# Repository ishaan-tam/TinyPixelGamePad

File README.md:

# TinyPixelGamePad
A tiny RP2040-powered handheld gamepad built around a custom SMD Neopixel matrix display. Designed to fit on a keychain and play simple retro-style games like Snake.

## Features
- Ultra-compact 20x12 Neopixel display using 1x1mm SMD LEDs
- RP2040 microcontroller
- Custom PCB designed in KiCad
- Programmed in Arduino
- USB-C power and programming
- Built-in games: Snake, with more to come

## Preview

## Repo Structure
- `Firmware/` – Game logic and display code (Arduino)
- `Hardware/` – KiCad schematics and PCB layout
- `Images/` – Rendered images and assembly photos
- `Docs/` – Build notes, game dev instructions

## Getting Started
1. Open `Firmware/snake.ino` in the Arduino IDE
2. Select the RP2040 board and upload via USB
3. Power on and start playing 

## Pin Mapping

## Roadmap
- Add menu for game selection
- Add buzzer for sound feedback
- Add charging support for LiPo battery
- Open-source arcade game template

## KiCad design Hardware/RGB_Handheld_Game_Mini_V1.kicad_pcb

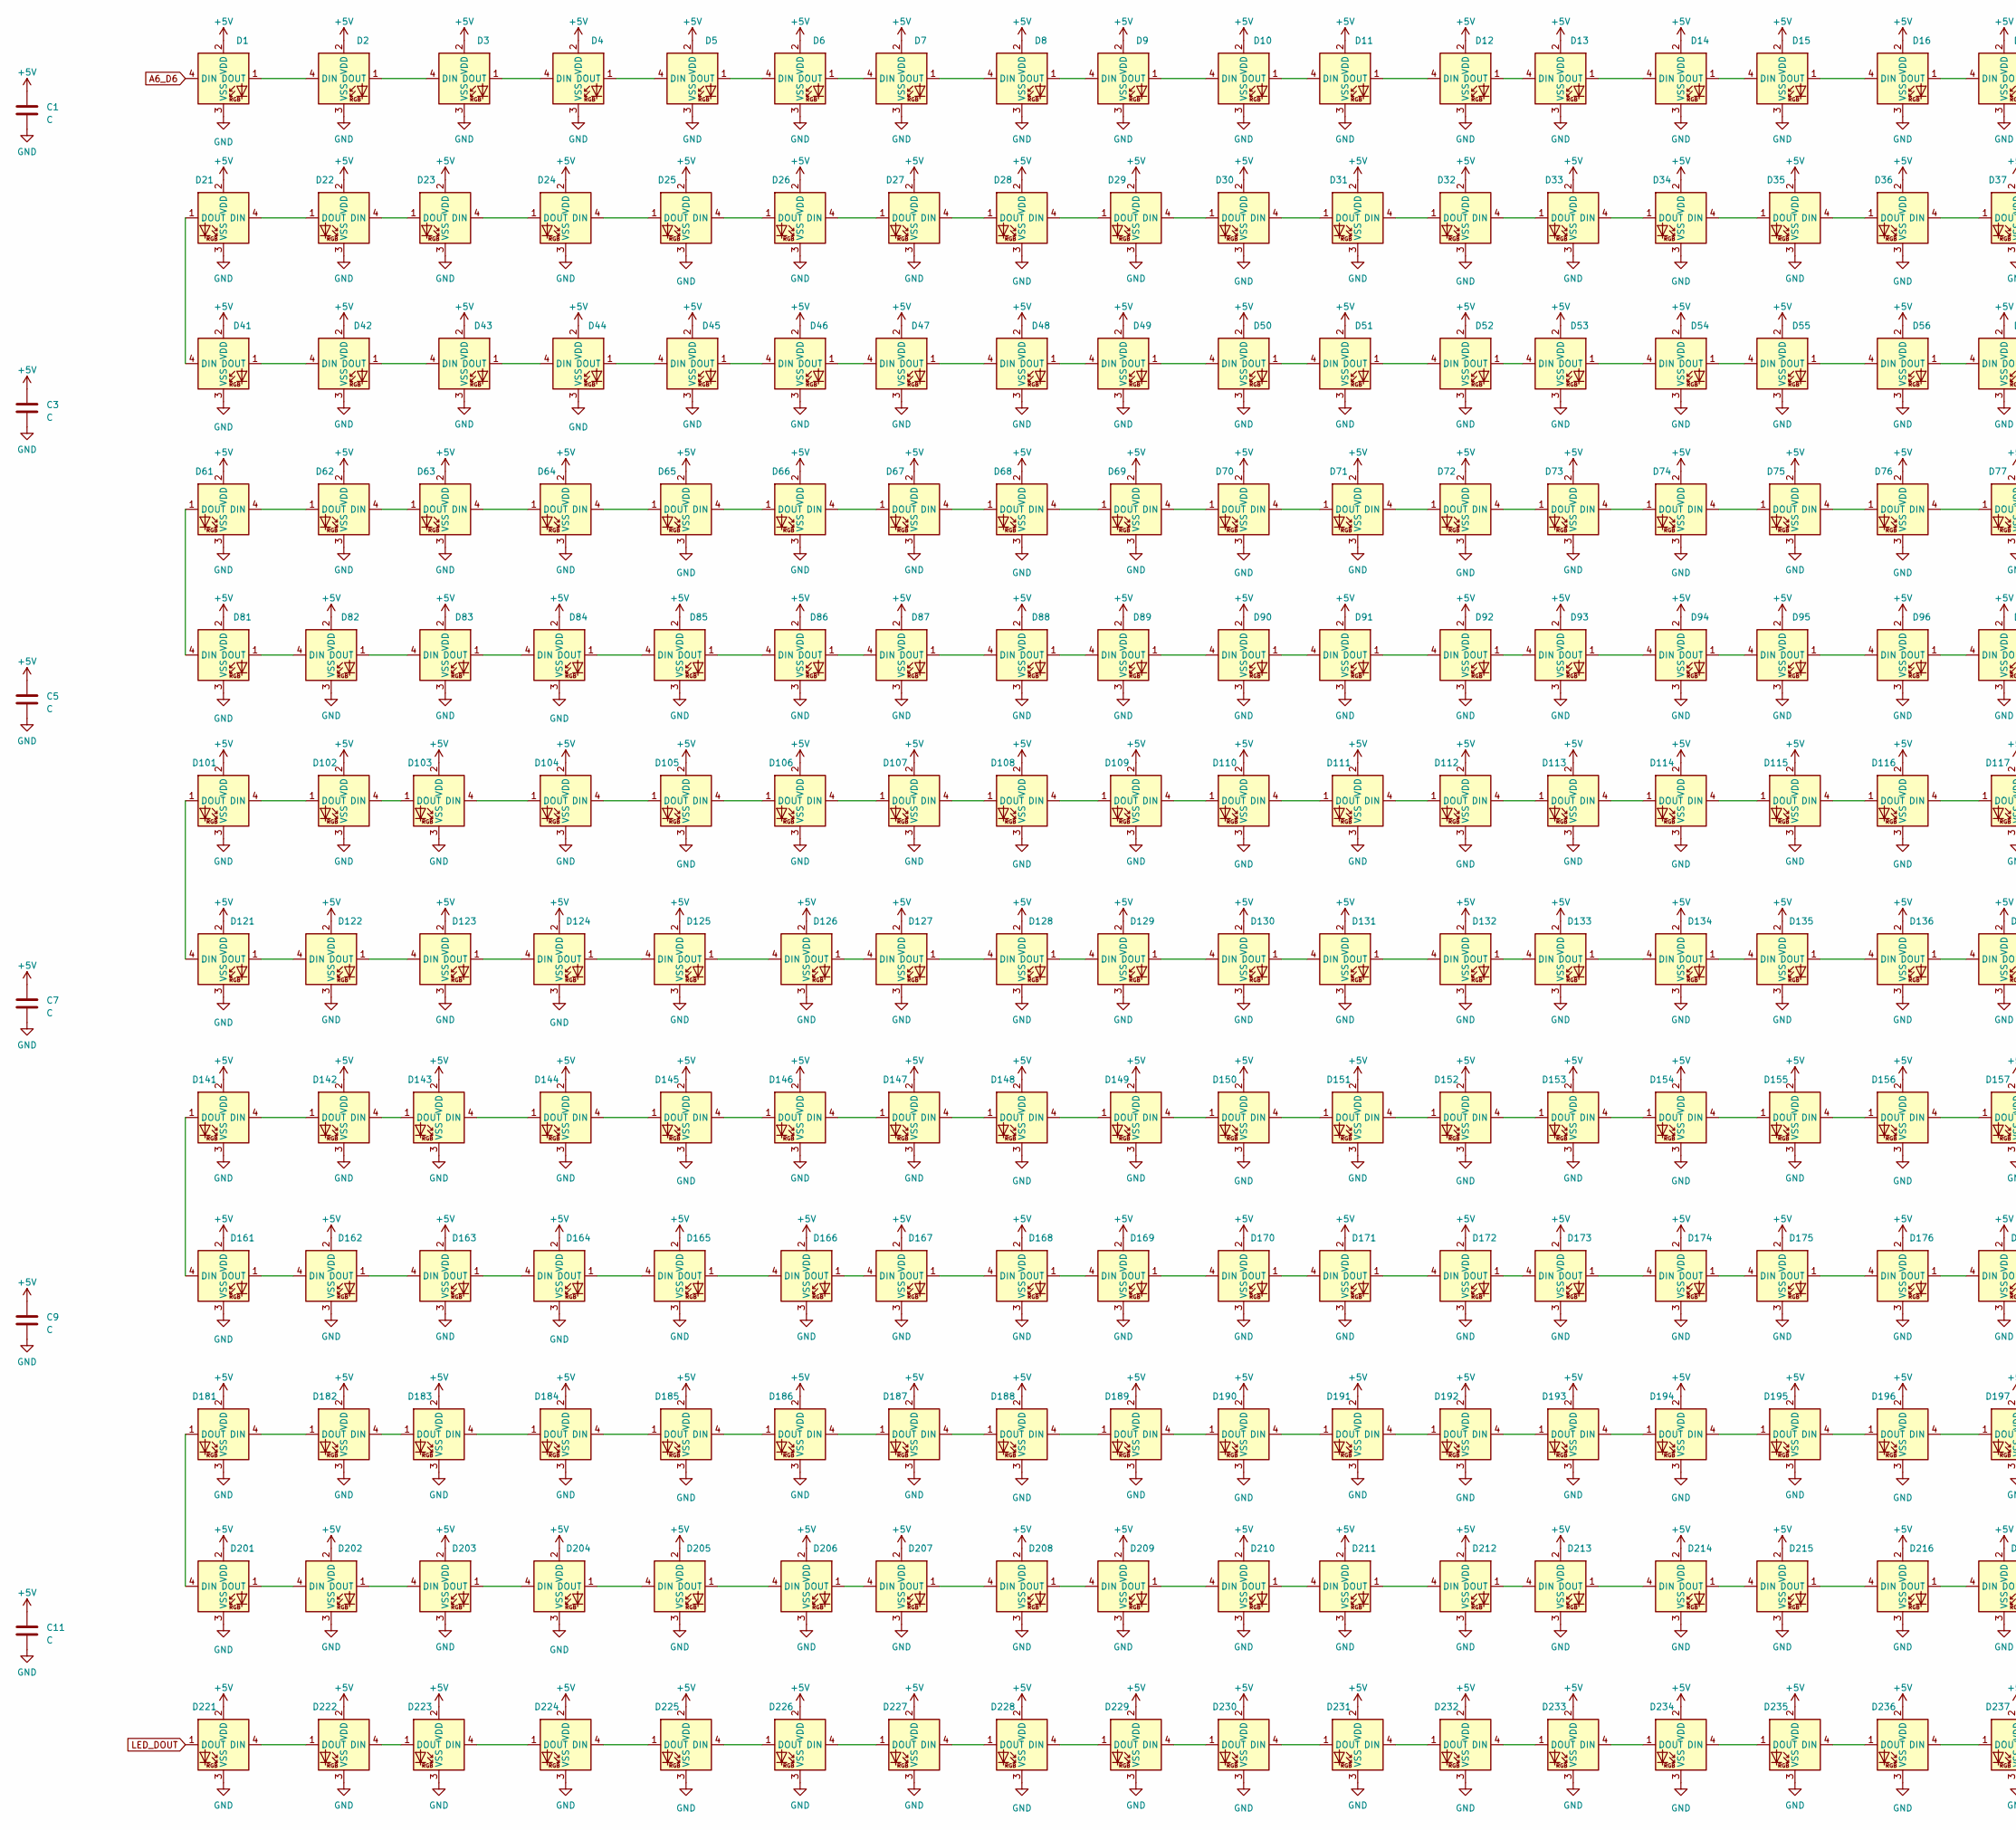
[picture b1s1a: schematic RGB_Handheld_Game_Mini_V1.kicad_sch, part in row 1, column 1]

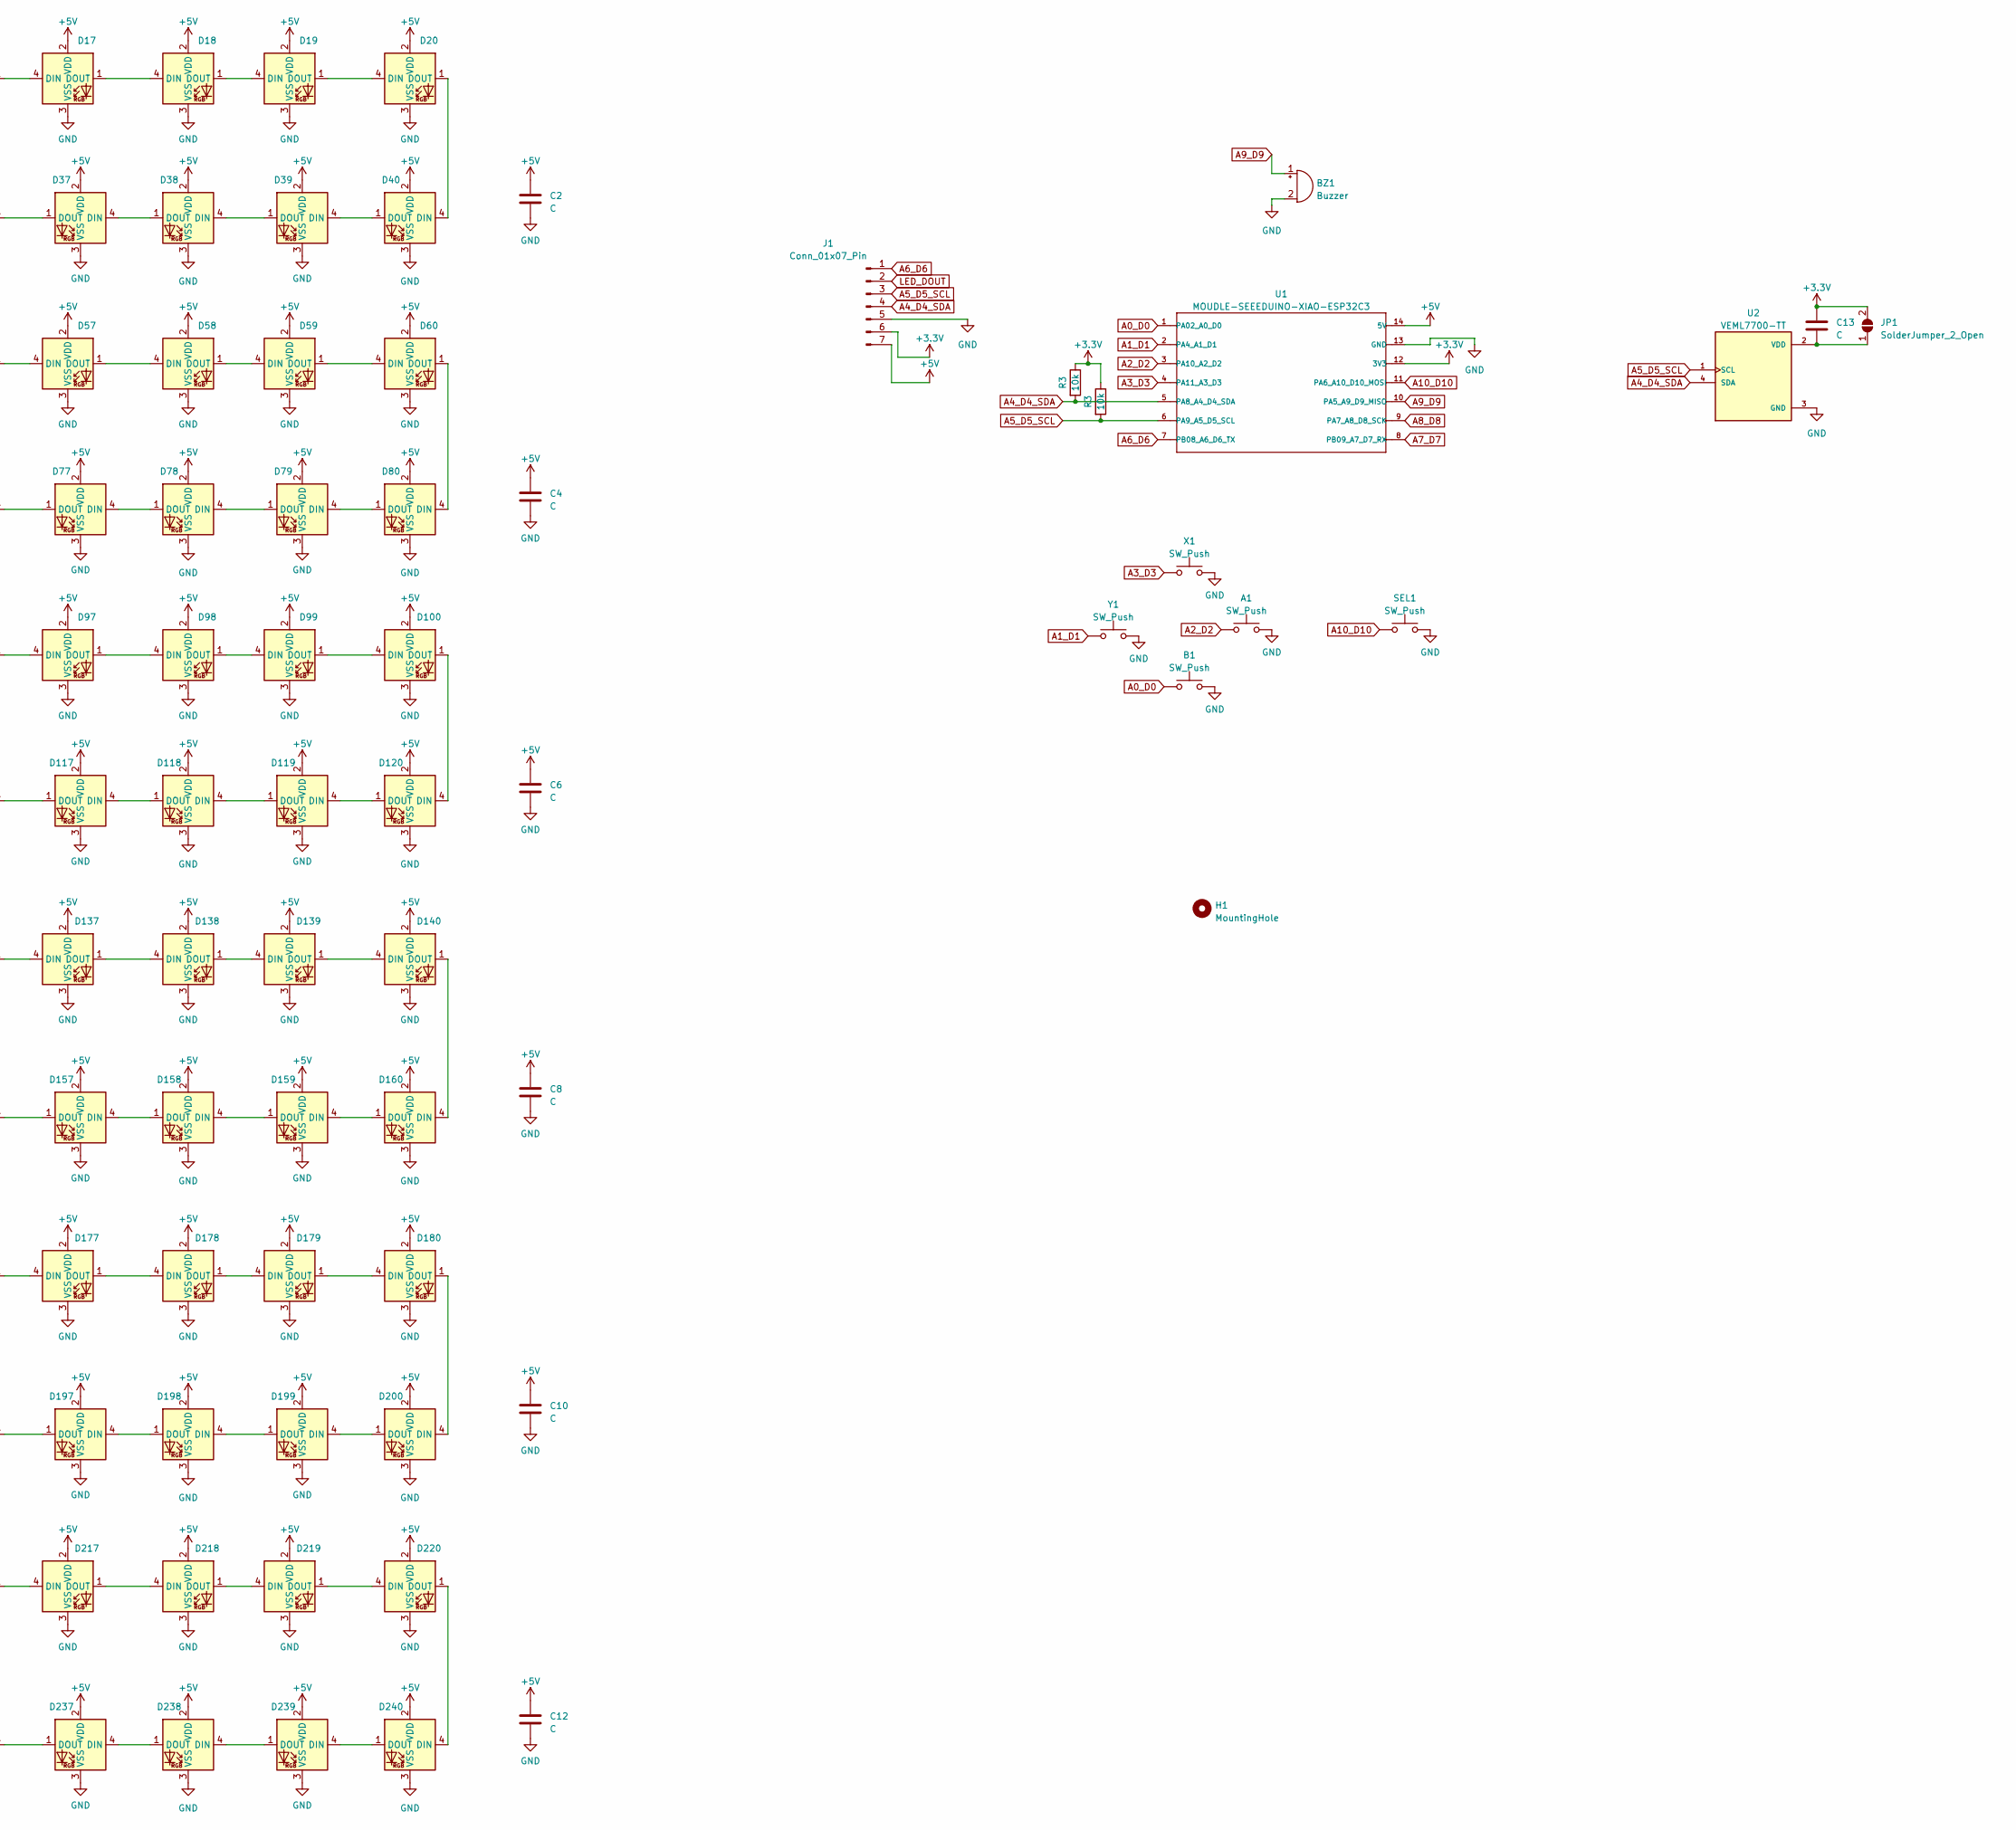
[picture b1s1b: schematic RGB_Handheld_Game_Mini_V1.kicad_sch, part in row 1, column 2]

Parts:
A1: SW_Push; SW_Tactile_SPST_NO_Straight_CK_PTS636Sx25SMTRLFS
B1: SW_Push; SW_Tactile_SPST_NO_Straight_CK_PTS636Sx25SMTRLFS
BZ1: Buzzer; Buzzer_Mallory_AST1109MLTRQ
C1, C2, C3, C4, C5, C6, C7, C8, C9, C10, C11, C12, C13: C; C_1206_3216Metric_Pad1.33x1.80mm_HandSolder
D1, D2, D3, D4, D5, D6, D7, D8, D9, D10, D11, D12, D13, D14, D15, D16, D17, D18, D19, D20, D21, D22, D23, D24, D25, D26, D27, D28, D29, D30, D31, D32, D33, D34, D35, D36, D37, D38, D39, D40, D41, D42, D43, D44, D45, D46, D47, D48, D49, D50, D51, D52, D53, D54, D55, D56, D57, D58, D59, D60, D61, D62, D63, D64, D65, D66, D67, D68, D69, D70, D71, D72, D73, D74, D75, D76, D77, D78, D79, D80, D81, D82, D83, D84, D85, D86, D87, D88, D89, D90, D91, D92, D93, D94, D95, D96, D97, D98, D99, D100, D101, D102, D103, D104, D105, D106, D107, D108, D109, D110, D111, D112, D113, D114, D115, D116, D117, D118, D119, D120, D121, D122, D123, D124, D125, D126, D127, D128, D129, D130, D131, D132, D133, D134, D135, D136, D137, D138, D139, D140, D141, D142, D143, D144, D145, D146, D147, D148, D149, D150, D151, D152, D153, D154, D155, D156, D157, D158, D159, D160, D161, D162, D163, D164, D165, D166, D167, D168, D169, D170, D171, D172, D173, D174, D175, D176, D177, D178, D179, D180, D181, D182, D183, D184, D185, D186, D187, D188, D189, D190, D191, D192, D193, D194, D195, D196, D197, D198, D199, D200, D201, D202, D203, D204, D205, D206, D207, D208, D209, D210, D211, D212, D213, D214, D215, D216, D217, D218, D219, D220, D221, D222, D223, D224, D225, D226, D227, D228, D229, D230, D231, D232, D233, D234, D235, D236, D237, D238, D239, D240: LED_SMD_1mmx1mm_JLC
H1: MountingHole; MountingHole_2.5mm
J1: Conn_01x07_Pin; PinSocket_1x07_P2.54mm_Vertical_SMD_Pin1Right
JP1: SolderJumper_2_Open; SolderJumper-2_P1.3mm_Open_RoundedPad1.0x1.5mm
R3: 10k; R_1206_3216Metric_Pad1.30x1.75mm_HandSolder
SEL1: SW_Push; SW_Tactile_SPST_NO_Straight_CK_PTS636Sx25SMTRLFS
U1: MOUDLE-SEEEDUINO-XIAO-ESP32C3; MODULE_xiao_ESP32_no_keepout
U2: VEML7700-TT; XDCR_VEML7700-TT; PARTREV 1.6
X1: SW_Push; SW_Tactile_SPST_NO_Straight_CK_PTS636Sx25SMTRLFS
Y1: SW_Push; SW_Tactile_SPST_NO_Straight_CK_PTS636Sx25SMTRLFS

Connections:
+3.3V: C13.1, J1.6, JP1.2 (B), U1.12 (3V3); also elsewhere on the board
+5V: C1.1, C2.1, C3.1, C4.1, C5.1, C6.1, C7.1, C8.1, C9.1, C10.1, C11.1, C12.1, D1.2 (VDD), D2.2 (VDD), D3.2 (VDD), D4.2 (VDD), D5.2 (VDD), D6.2 (VDD), D7.2 (VDD), D8.2 (VDD), D9.2 (VDD), D10.2 (VDD), D11.2 (VDD), D12.2 (VDD), D13.2 (VDD), D14.2 (VDD), D15.2 (VDD), D16.2 (VDD), D17.2 (VDD), D18.2 (VDD), D19.2 (VDD), D20.2 (VDD), D21.2 (VDD), D22.2 (VDD), D23.2 (VDD), D24.2 (VDD), D25.2 (VDD), D26.2 (VDD), D27.2 (VDD), D28.2 (VDD), D29.2 (VDD), D30.2 (VDD), D31.2 (VDD), D32.2 (VDD), D33.2 (VDD), D34.2 (VDD), D35.2 (VDD), D36.2 (VDD), D37.2 (VDD), D38.2 (VDD), D39.2 (VDD), D40.2 (VDD), D41.2 (VDD), D42.2 (VDD), D43.2 (VDD), D44.2 (VDD), D45.2 (VDD), D46.2 (VDD), D47.2 (VDD), D48.2 (VDD), D49.2 (VDD), D50.2 (VDD), D51.2 (VDD), D52.2 (VDD), D53.2 (VDD), D54.2 (VDD), D55.2 (VDD), D56.2 (VDD), D57.2 (VDD), D58.2 (VDD), D59.2 (VDD), D60.2 (VDD), D61.2 (VDD), D62.2 (VDD), D63.2 (VDD), D64.2 (VDD), D65.2 (VDD), D66.2 (VDD), D67.2 (VDD), D68.2 (VDD), D69.2 (VDD), D70.2 (VDD), D71.2 (VDD), D72.2 (VDD), D73.2 (VDD), D74.2 (VDD), D75.2 (VDD), D76.2 (VDD), D77.2 (VDD), D78.2 (VDD), D79.2 (VDD), D80.2 (VDD), D81.2 (VDD), D82.2 (VDD), D83.2 (VDD), D84.2 (VDD), D85.2 (VDD), D86.2 (VDD), D87.2 (VDD), D88.2 (VDD), D89.2 (VDD), D90.2 (VDD), D91.2 (VDD), D92.2 (VDD), D93.2 (VDD), D94.2 (VDD), D95.2 (VDD), D96.2 (VDD), D97.2 (VDD), D98.2 (VDD), D99.2 (VDD), D100.2 (VDD), D101.2 (VDD), D102.2 (VDD), D103.2 (VDD), D104.2 (VDD), D105.2 (VDD), D106.2 (VDD), D107.2 (VDD), D108.2 (VDD), D109.2 (VDD), D110.2 (VDD), D111.2 (VDD), D112.2 (VDD), D113.2 (VDD), D114.2 (VDD), D115.2 (VDD), D116.2 (VDD), D117.2 (VDD), D118.2 (VDD), D119.2 (VDD), D120.2 (VDD), D121.2 (VDD), D122.2 (VDD), D123.2 (VDD), D124.2 (VDD), D125.2 (VDD), D126.2 (VDD), D127.2 (VDD), D128.2 (VDD), D129.2 (VDD), D130.2 (VDD), D131.2 (VDD), D132.2 (VDD), D133.2 (VDD), D134.2 (VDD), D135.2 (VDD), D136.2 (VDD), D137.2 (VDD), D138.2 (VDD), D139.2 (VDD), D140.2 (VDD), D141.2 (VDD), D142.2 (VDD), D143.2 (VDD), D144.2 (VDD), D145.2 (VDD), D146.2 (VDD), D147.2 (VDD), D148.2 (VDD), D149.2 (VDD), D150.2 (VDD), D151.2 (VDD), D152.2 (VDD), D153.2 (VDD), D154.2 (VDD), D155.2 (VDD), D156.2 (VDD), D157.2 (VDD), D158.2 (VDD), D159.2 (VDD), D160.2 (VDD), D161.2 (VDD), D162.2 (VDD), D163.2 (VDD), D164.2 (VDD), D165.2 (VDD), D166.2 (VDD), D167.2 (VDD), D168.2 (VDD), D169.2 (VDD), D170.2 (VDD), D171.2 (VDD), D172.2 (VDD), D173.2 (VDD), D174.2 (VDD), D175.2 (VDD), D176.2 (VDD), D177.2 (VDD), D178.2 (VDD), D179.2 (VDD), D180.2 (VDD), D181.2 (VDD), D182.2 (VDD), D183.2 (VDD), D184.2 (VDD), D185.2 (VDD), D186.2 (VDD), D187.2 (VDD), D188.2 (VDD), D189.2 (VDD), D190.2 (VDD), D191.2 (VDD), D192.2 (VDD), D193.2 (VDD), D194.2 (VDD), D195.2 (VDD), D196.2 (VDD), D197.2 (VDD), D198.2 (VDD), D199.2 (VDD), D200.2 (VDD), D201.2 (VDD), D202.2 (VDD), D203.2 (VDD), D204.2 (VDD), D205.2 (VDD), D206.2 (VDD), D207.2 (VDD), D208.2 (VDD), D209.2 (VDD), D210.2 (VDD), D211.2 (VDD), D212.2 (VDD), D213.2 (VDD), D214.2 (VDD), D215.2 (VDD), D216.2 (VDD), D217.2 (VDD), D218.2 (VDD), D219.2 (VDD), D220.2 (VDD), D221.2 (VDD), D222.2 (VDD), D223.2 (VDD), D224.2 (VDD), D225.2 (VDD), D226.2 (VDD), D227.2 (VDD), D228.2 (VDD), D229.2 (VDD), D230.2 (VDD), D231.2 (VDD), D232.2 (VDD), D233.2 (VDD), D234.2 (VDD), D235.2 (VDD), D236.2 (VDD), D237.2 (VDD), D238.2 (VDD), D239.2 (VDD), D240.2 (VDD), J1.7, U1.14 (5V)
A0_D0: B1.2, U1.1 (PA02_A0_D0)
A1_D1: U1.2 (PA4_A1_D1), Y1.2
A2_D2: A1.2, U1.3 (PA10_A2_D2)
A3_D3: U1.4 (PA11_A3_D3), X1.2
A6_D6: D1.4 (DIN), J1.1, U1.7 (PB08_A6_D6_TX)
A7_D7: U1.8 (PB09_A7_D7_RX)
A8_D8: U1.9 (PA7_A8_D8_SCK)
A9_D9: BZ1.1 (-), U1.10 (PA5_A9_D9_MISO)
A10_D10: SEL1.2, U1.11 (PA6_A10_D10_MOSI)
GND: A1.1, B1.1, BZ1.2 (+), C1.2, C2.2, C3.2, C4.2, C5.2, C6.2, C7.2, C8.2, C9.2, C10.2, C11.2, C12.2, D1.3 (VSS), D2.3 (VSS), D3.3 (VSS), D4.3 (VSS), D5.3 (VSS), D6.3 (VSS), D7.3 (VSS), D8.3 (VSS), D9.3 (VSS), D10.3 (VSS), D11.3 (VSS), D12.3 (VSS), D13.3 (VSS), D14.3 (VSS), D15.3 (VSS), D16.3 (VSS), D17.3 (VSS), D18.3 (VSS), D19.3 (VSS), D20.3 (VSS), D21.3 (VSS), D22.3 (VSS), D23.3 (VSS), D24.3 (VSS), D25.3 (VSS), D26.3 (VSS), D27.3 (VSS), D28.3 (VSS), D29.3 (VSS), D30.3 (VSS), D31.3 (VSS), D32.3 (VSS), D33.3 (VSS), D34.3 (VSS), D35.3 (VSS), D36.3 (VSS), D37.3 (VSS), D38.3 (VSS), D39.3 (VSS), D40.3 (VSS), D41.3 (VSS), D42.3 (VSS), D43.3 (VSS), D44.3 (VSS), D45.3 (VSS), D46.3 (VSS), D47.3 (VSS), D48.3 (VSS), D49.3 (VSS), D50.3 (VSS), D51.3 (VSS), D52.3 (VSS), D53.3 (VSS), D54.3 (VSS), D55.3 (VSS), D56.3 (VSS), D57.3 (VSS), D58.3 (VSS), D59.3 (VSS), D60.3 (VSS), D61.3 (VSS), D62.3 (VSS), D63.3 (VSS), D64.3 (VSS), D65.3 (VSS), D66.3 (VSS), D67.3 (VSS), D68.3 (VSS), D69.3 (VSS), D70.3 (VSS), D71.3 (VSS), D72.3 (VSS), D73.3 (VSS), D74.3 (VSS), D75.3 (VSS), D76.3 (VSS), D77.3 (VSS), D78.3 (VSS), D79.3 (VSS), D80.3 (VSS), D81.3 (VSS), D82.3 (VSS), D83.3 (VSS), D84.3 (VSS), D85.3 (VSS), D86.3 (VSS), D87.3 (VSS), D88.3 (VSS), D89.3 (VSS), D90.3 (VSS), D91.3 (VSS), D92.3 (VSS), D93.3 (VSS), D94.3 (VSS), D95.3 (VSS), D96.3 (VSS), D97.3 (VSS), D98.3 (VSS), D99.3 (VSS), D100.3 (VSS), D101.3 (VSS), D102.3 (VSS), D103.3 (VSS), D104.3 (VSS), D105.3 (VSS), D106.3 (VSS), D107.3 (VSS), D108.3 (VSS), D109.3 (VSS), D110.3 (VSS), D111.3 (VSS), D112.3 (VSS), D113.3 (VSS), D114.3 (VSS), D115.3 (VSS), D116.3 (VSS), D117.3 (VSS), D118.3 (VSS), D119.3 (VSS), D120.3 (VSS), D121.3 (VSS), D122.3 (VSS), D123.3 (VSS), D124.3 (VSS), D125.3 (VSS), D126.3 (VSS), D127.3 (VSS), D128.3 (VSS), D129.3 (VSS), D130.3 (VSS), D131.3 (VSS), D132.3 (VSS), D133.3 (VSS), D134.3 (VSS), D135.3 (VSS), D136.3 (VSS), D137.3 (VSS), D138.3 (VSS), D139.3 (VSS), D140.3 (VSS), D141.3 (VSS), D142.3 (VSS), D143.3 (VSS), D144.3 (VSS), D145.3 (VSS), D146.3 (VSS), D147.3 (VSS), D148.3 (VSS), D149.3 (VSS), D150.3 (VSS), D151.3 (VSS), D152.3 (VSS), D153.3 (VSS), D154.3 (VSS), D155.3 (VSS), D156.3 (VSS), D157.3 (VSS), D158.3 (VSS), D159.3 (VSS), D160.3 (VSS), D161.3 (VSS), D162.3 (VSS), D163.3 (VSS), D164.3 (VSS), D165.3 (VSS), D166.3 (VSS), D167.3 (VSS), D168.3 (VSS), D169.3 (VSS), D170.3 (VSS), D171.3 (VSS), D172.3 (VSS), D173.3 (VSS), D174.3 (VSS), D175.3 (VSS), D176.3 (VSS), D177.3 (VSS), D178.3 (VSS), D179.3 (VSS), D180.3 (VSS), D181.3 (VSS), D182.3 (VSS), D183.3 (VSS), D184.3 (VSS), D185.3 (VSS), D186.3 (VSS), D187.3 (VSS), D188.3 (VSS), D189.3 (VSS), D190.3 (VSS), D191.3 (VSS), D192.3 (VSS), D193.3 (VSS), D194.3 (VSS), D195.3 (VSS), D196.3 (VSS), D197.3 (VSS), D198.3 (VSS), D199.3 (VSS), D200.3 (VSS), D201.3 (VSS), D202.3 (VSS), D203.3 (VSS), D204.3 (VSS), D205.3 (VSS), D206.3 (VSS), D207.3 (VSS), D208.3 (VSS), D209.3 (VSS), D210.3 (VSS), D211.3 (VSS), D212.3 (VSS), D213.3 (VSS), D214.3 (VSS), D215.3 (VSS), D216.3 (VSS), D217.3 (VSS), D218.3 (VSS), D219.3 (VSS), D220.3 (VSS), D221.3 (VSS), D222.3 (VSS), D223.3 (VSS), D224.3 (VSS), D225.3 (VSS), D226.3 (VSS), D227.3 (VSS), D228.3 (VSS), D229.3 (VSS), D230.3 (VSS), D231.3 (VSS), D232.3 (VSS), D233.3 (VSS), D234.3 (VSS), D235.3 (VSS), D236.3 (VSS), D237.3 (VSS), D238.3 (VSS), D239.3 (VSS), D240.3 (VSS), J1.5, SEL1.1, U1.13 (GND), U2.3 (GND), X1.1, Y1.1
LED_DOUT: D221.1 (DOUT), J1.2
unnamed: D1.1 (DOUT), D2.4 (DIN)
unnamed: D2.1 (DOUT), D3.4 (DIN)
unnamed: D3.1 (DOUT), D4.4 (DIN)
unnamed: D4.1 (DOUT), D5.4 (DIN)
unnamed: D5.1 (DOUT), D6.4 (DIN)
unnamed: D6.1 (DOUT), D7.4 (DIN)
unnamed: D7.1 (DOUT), D8.4 (DIN)
unnamed: D8.1 (DOUT), D9.4 (DIN)
unnamed: D9.1 (DOUT), D10.4 (DIN)
unnamed: D10.1 (DOUT), D11.4 (DIN)
unnamed: D11.1 (DOUT), D12.4 (DIN)
unnamed: D12.1 (DOUT), D13.4 (DIN)
unnamed: D13.1 (DOUT), D14.4 (DIN)
unnamed: D14.1 (DOUT), D15.4 (DIN)
unnamed: D15.1 (DOUT), D16.4 (DIN)
unnamed: D16.1 (DOUT), D17.4 (DIN)
unnamed: D17.1 (DOUT), D18.4 (DIN)
unnamed: D18.1 (DOUT), D19.4 (DIN)
unnamed: D19.1 (DOUT), D20.4 (DIN)
unnamed: D20.1 (DOUT), D40.4 (DIN)
unnamed: D21.4 (DIN), D22.1 (DOUT)
unnamed: D21.1 (DOUT), D41.4 (DIN)
unnamed: D22.4 (DIN), D23.1 (DOUT)
unnamed: D23.4 (DIN), D24.1 (DOUT)
unnamed: D24.4 (DIN), D25.1 (DOUT)
unnamed: D25.4 (DIN), D26.1 (DOUT)
unnamed: D26.4 (DIN), D27.1 (DOUT)
unnamed: D27.4 (DIN), D28.1 (DOUT)
unnamed: D28.4 (DIN), D29.1 (DOUT)
unnamed: D29.4 (DIN), D30.1 (DOUT)
unnamed: D30.4 (DIN), D31.1 (DOUT)
unnamed: D31.4 (DIN), D32.1 (DOUT)
unnamed: D32.4 (DIN), D33.1 (DOUT)
unnamed: D33.4 (DIN), D34.1 (DOUT)
unnamed: D34.4 (DIN), D35.1 (DOUT)
unnamed: D35.4 (DIN), D36.1 (DOUT)
unnamed: D36.4 (DIN), D37.1 (DOUT)
unnamed: D37.4 (DIN), D38.1 (DOUT)
unnamed: D38.4 (DIN), D39.1 (DOUT)
unnamed: D39.4 (DIN), D40.1 (DOUT)
unnamed: D41.1 (DOUT), D42.4 (DIN)
unnamed: D42.1 (DOUT), D43.4 (DIN)
unnamed: D43.1 (DOUT), D44.4 (DIN)
unnamed: D44.1 (DOUT), D45.4 (DIN)
unnamed: D45.1 (DOUT), D46.4 (DIN)
unnamed: D46.1 (DOUT), D47.4 (DIN)
unnamed: D47.1 (DOUT), D48.4 (DIN)
unnamed: D48.1 (DOUT), D49.4 (DIN)
unnamed: D49.1 (DOUT), D50.4 (DIN)
unnamed: D50.1 (DOUT), D51.4 (DIN)
unnamed: D51.1 (DOUT), D52.4 (DIN)
unnamed: D52.1 (DOUT), D53.4 (DIN)
unnamed: D53.1 (DOUT), D54.4 (DIN)
unnamed: D54.1 (DOUT), D55.4 (DIN)
unnamed: D55.1 (DOUT), D56.4 (DIN)
unnamed: D56.1 (DOUT), D57.4 (DIN)
unnamed: D57.1 (DOUT), D58.4 (DIN)
unnamed: D58.1 (DOUT), D59.4 (DIN)
unnamed: D59.1 (DOUT), D60.4 (DIN)
unnamed: D60.1 (DOUT), D80.4 (DIN)
unnamed: D61.4 (DIN), D62.1 (DOUT)
unnamed: D61.1 (DOUT), D81.4 (DIN)
unnamed: D62.4 (DIN), D63.1 (DOUT)
unnamed: D63.4 (DIN), D64.1 (DOUT)
unnamed: D64.4 (DIN), D65.1 (DOUT)
unnamed: D65.4 (DIN), D66.1 (DOUT)
unnamed: D66.4 (DIN), D67.1 (DOUT)
unnamed: D67.4 (DIN), D68.1 (DOUT)
unnamed: D68.4 (DIN), D69.1 (DOUT)
unnamed: D69.4 (DIN), D70.1 (DOUT)
unnamed: D70.4 (DIN), D71.1 (DOUT)
unnamed: D71.4 (DIN), D72.1 (DOUT)
unnamed: D72.4 (DIN), D73.1 (DOUT)
unnamed: D73.4 (DIN), D74.1 (DOUT)
unnamed: D74.4 (DIN), D75.1 (DOUT)
unnamed: D75.4 (DIN), D76.1 (DOUT)
unnamed: D76.4 (DIN), D77.1 (DOUT)
unnamed: D77.4 (DIN), D78.1 (DOUT)
unnamed: D78.4 (DIN), D79.1 (DOUT)
unnamed: D79.4 (DIN), D80.1 (DOUT)
unnamed: D81.1 (DOUT), D82.4 (DIN)
unnamed: D82.1 (DOUT), D83.4 (DIN)
unnamed: D83.1 (DOUT), D84.4 (DIN)
unnamed: D84.1 (DOUT), D85.4 (DIN)
unnamed: D85.1 (DOUT), D86.4 (DIN)
unnamed: D86.1 (DOUT), D87.4 (DIN)
unnamed: D87.1 (DOUT), D88.4 (DIN)
unnamed: D88.1 (DOUT), D89.4 (DIN)
unnamed: D89.1 (DOUT), D90.4 (DIN)
unnamed: D90.1 (DOUT), D91.4 (DIN)
unnamed: D91.1 (DOUT), D92.4 (DIN)
unnamed: D92.1 (DOUT), D93.4 (DIN)
unnamed: D93.1 (DOUT), D94.4 (DIN)
unnamed: D94.1 (DOUT), D95.4 (DIN)
unnamed: D95.1 (DOUT), D96.4 (DIN)
unnamed: D96.1 (DOUT), D97.4 (DIN)
unnamed: D97.1 (DOUT), D98.4 (DIN)
unnamed: D98.1 (DOUT), D99.4 (DIN)
unnamed: D99.1 (DOUT), D100.4 (DIN)
unnamed: D100.1 (DOUT), D120.4 (DIN)
unnamed: D101.4 (DIN), D102.1 (DOUT)
unnamed: D101.1 (DOUT), D121.4 (DIN)
unnamed: D102.4 (DIN), D103.1 (DOUT)
unnamed: D103.4 (DIN), D104.1 (DOUT)
unnamed: D104.4 (DIN), D105.1 (DOUT)
unnamed: D105.4 (DIN), D106.1 (DOUT)
unnamed: D106.4 (DIN), D107.1 (DOUT)
unnamed: D107.4 (DIN), D108.1 (DOUT)
unnamed: D108.4 (DIN), D109.1 (DOUT)
unnamed: D109.4 (DIN), D110.1 (DOUT)
unnamed: D110.4 (DIN), D111.1 (DOUT)
unnamed: D111.4 (DIN), D112.1 (DOUT)
unnamed: D112.4 (DIN), D113.1 (DOUT)
unnamed: D113.4 (DIN), D114.1 (DOUT)
unnamed: D114.4 (DIN), D115.1 (DOUT)
unnamed: D115.4 (DIN), D116.1 (DOUT)
unnamed: D116.4 (DIN), D117.1 (DOUT)
unnamed: D117.4 (DIN), D118.1 (DOUT)
unnamed: D118.4 (DIN), D119.1 (DOUT)
unnamed: D119.4 (DIN), D120.1 (DOUT)
unnamed: D121.1 (DOUT), D122.4 (DIN)
unnamed: D122.1 (DOUT), D123.4 (DIN)
unnamed: D123.1 (DOUT), D124.4 (DIN)
unnamed: D124.1 (DOUT), D125.4 (DIN)
unnamed: D125.1 (DOUT), D126.4 (DIN)
unnamed: D126.1 (DOUT), D127.4 (DIN)
unnamed: D127.1 (DOUT), D128.4 (DIN)
unnamed: D128.1 (DOUT), D129.4 (DIN)
unnamed: D129.1 (DOUT), D130.4 (DIN)
unnamed: D130.1 (DOUT), D131.4 (DIN)
unnamed: D131.1 (DOUT), D132.4 (DIN)
unnamed: D132.1 (DOUT), D133.4 (DIN)
unnamed: D133.1 (DOUT), D134.4 (DIN)
unnamed: D134.1 (DOUT), D135.4 (DIN)
unnamed: D135.1 (DOUT), D136.4 (DIN)
unnamed: D136.1 (DOUT), D137.4 (DIN)
unnamed: D137.1 (DOUT), D138.4 (DIN)
unnamed: D138.1 (DOUT), D139.4 (DIN)
unnamed: D139.1 (DOUT), D140.4 (DIN)
unnamed: D140.1 (DOUT), D160.4 (DIN)
unnamed: D141.4 (DIN), D142.1 (DOUT)
unnamed: D141.1 (DOUT), D161.4 (DIN)
unnamed: D142.4 (DIN), D143.1 (DOUT)
unnamed: D143.4 (DIN), D144.1 (DOUT)
unnamed: D144.4 (DIN), D145.1 (DOUT)
unnamed: D145.4 (DIN), D146.1 (DOUT)
unnamed: D146.4 (DIN), D147.1 (DOUT)
unnamed: D147.4 (DIN), D148.1 (DOUT)
unnamed: D148.4 (DIN), D149.1 (DOUT)
unnamed: D149.4 (DIN), D150.1 (DOUT)
unnamed: D150.4 (DIN), D151.1 (DOUT)
unnamed: D151.4 (DIN), D152.1 (DOUT)
unnamed: D152.4 (DIN), D153.1 (DOUT)
unnamed: D153.4 (DIN), D154.1 (DOUT)
unnamed: D154.4 (DIN), D155.1 (DOUT)
unnamed: D155.4 (DIN), D156.1 (DOUT)
unnamed: D156.4 (DIN), D157.1 (DOUT)
unnamed: D157.4 (DIN), D158.1 (DOUT)
unnamed: D158.4 (DIN), D159.1 (DOUT)
unnamed: D159.4 (DIN), D160.1 (DOUT)
unnamed: D161.1 (DOUT), D162.4 (DIN)
unnamed: D162.1 (DOUT), D163.4 (DIN)
unnamed: D163.1 (DOUT), D164.4 (DIN)
unnamed: D164.1 (DOUT), D165.4 (DIN)
unnamed: D165.1 (DOUT), D166.4 (DIN)
unnamed: D166.1 (DOUT), D167.4 (DIN)
unnamed: D167.1 (DOUT), D168.4 (DIN)
unnamed: D168.1 (DOUT), D169.4 (DIN)
unnamed: D169.1 (DOUT), D170.4 (DIN)
unnamed: D170.1 (DOUT), D171.4 (DIN)
unnamed: D171.1 (DOUT), D172.4 (DIN)
unnamed: D172.1 (DOUT), D173.4 (DIN)
unnamed: D173.1 (DOUT), D174.4 (DIN)
unnamed: D174.1 (DOUT), D175.4 (DIN)
unnamed: D175.1 (DOUT), D176.4 (DIN)
unnamed: D176.1 (DOUT), D177.4 (DIN)
unnamed: D177.1 (DOUT), D178.4 (DIN)
unnamed: D178.1 (DOUT), D179.4 (DIN)
unnamed: D179.1 (DOUT), D180.4 (DIN)
unnamed: D180.1 (DOUT), D200.4 (DIN)
unnamed: D181.4 (DIN), D182.1 (DOUT)
unnamed: D181.1 (DOUT), D201.4 (DIN)
unnamed: D182.4 (DIN), D183.1 (DOUT)
unnamed: D183.4 (DIN), D184.1 (DOUT)
unnamed: D184.4 (DIN), D185.1 (DOUT)
unnamed: D185.4 (DIN), D186.1 (DOUT)
unnamed: D186.4 (DIN), D187.1 (DOUT)
unnamed: D187.4 (DIN), D188.1 (DOUT)
unnamed: D188.4 (DIN), D189.1 (DOUT)
unnamed: D189.4 (DIN), D190.1 (DOUT)
unnamed: D190.4 (DIN), D191.1 (DOUT)
unnamed: D191.4 (DIN), D192.1 (DOUT)
unnamed: D192.4 (DIN), D193.1 (DOUT)
unnamed: D193.4 (DIN), D194.1 (DOUT)
unnamed: D194.4 (DIN), D195.1 (DOUT)
unnamed: D195.4 (DIN), D196.1 (DOUT)
unnamed: D196.4 (DIN), D197.1 (DOUT)
unnamed: D197.4 (DIN), D198.1 (DOUT)
unnamed: D198.4 (DIN), D199.1 (DOUT)
unnamed: D199.4 (DIN), D200.1 (DOUT)
unnamed: D201.1 (DOUT), D202.4 (DIN)
unnamed: D202.1 (DOUT), D203.4 (DIN)
unnamed: D203.1 (DOUT), D204.4 (DIN)
unnamed: D204.1 (DOUT), D205.4 (DIN)
unnamed: D205.1 (DOUT), D206.4 (DIN)
unnamed: D206.1 (DOUT), D207.4 (DIN)
unnamed: D207.1 (DOUT), D208.4 (DIN)
unnamed: D208.1 (DOUT), D209.4 (DIN)
unnamed: D209.1 (DOUT), D210.4 (DIN)
unnamed: D210.1 (DOUT), D211.4 (DIN)
unnamed: D211.1 (DOUT), D212.4 (DIN)
unnamed: D212.1 (DOUT), D213.4 (DIN)
unnamed: D213.1 (DOUT), D214.4 (DIN)
unnamed: D214.1 (DOUT), D215.4 (DIN)
unnamed: D215.1 (DOUT), D216.4 (DIN)
unnamed: D216.1 (DOUT), D217.4 (DIN)
unnamed: D217.1 (DOUT), D218.4 (DIN)
unnamed: D218.1 (DOUT), D219.4 (DIN)
unnamed: D219.1 (DOUT), D220.4 (DIN)
unnamed: D220.1 (DOUT), D240.4 (DIN)
unnamed: D221.4 (DIN), D222.1 (DOUT)
unnamed: D222.4 (DIN), D223.1 (DOUT)
unnamed: D223.4 (DIN), D224.1 (DOUT)
unnamed: D224.4 (DIN), D225.1 (DOUT)
unnamed: D225.4 (DIN), D226.1 (DOUT)
unnamed: D226.4 (DIN), D227.1 (DOUT)
unnamed: D227.4 (DIN), D228.1 (DOUT)
unnamed: D228.4 (DIN), D229.1 (DOUT)
unnamed: D229.4 (DIN), D230.1 (DOUT)
unnamed: D230.4 (DIN), D231.1 (DOUT)
unnamed: D231.4 (DIN), D232.1 (DOUT)
unnamed: D232.4 (DIN), D233.1 (DOUT)
unnamed: D233.4 (DIN), D234.1 (DOUT)
unnamed: D234.4 (DIN), D235.1 (DOUT)
unnamed: D235.4 (DIN), D236.1 (DOUT)
unnamed: D236.4 (DIN), D237.1 (DOUT)
unnamed: D237.4 (DIN), D238.1 (DOUT)
unnamed: D238.4 (DIN), D239.1 (DOUT)
unnamed: D239.4 (DIN), D240.1 (DOUT)
unnamed: C13.2, JP1.1 (A), U2.2 (VDD)

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
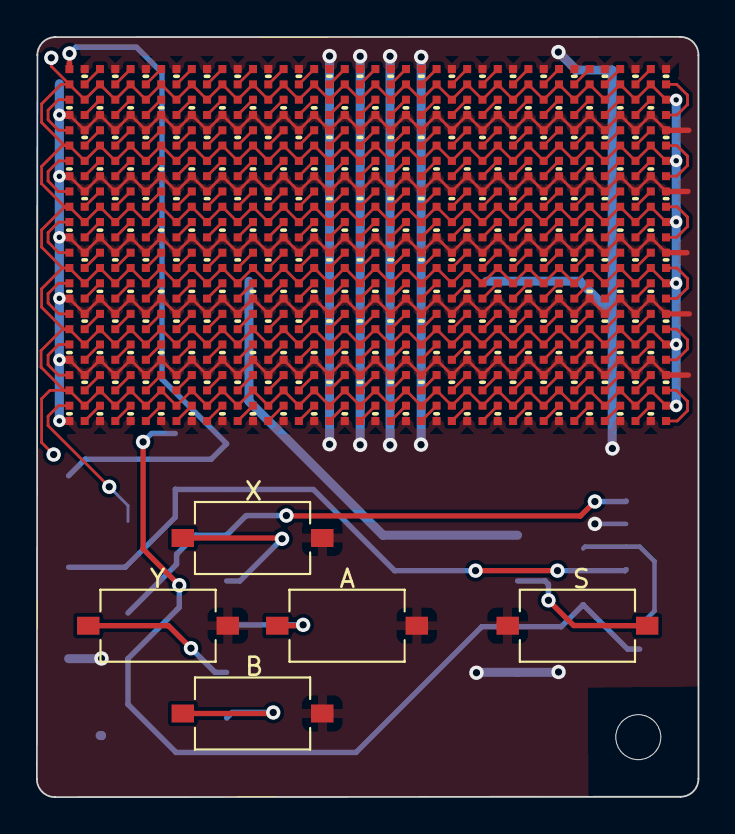
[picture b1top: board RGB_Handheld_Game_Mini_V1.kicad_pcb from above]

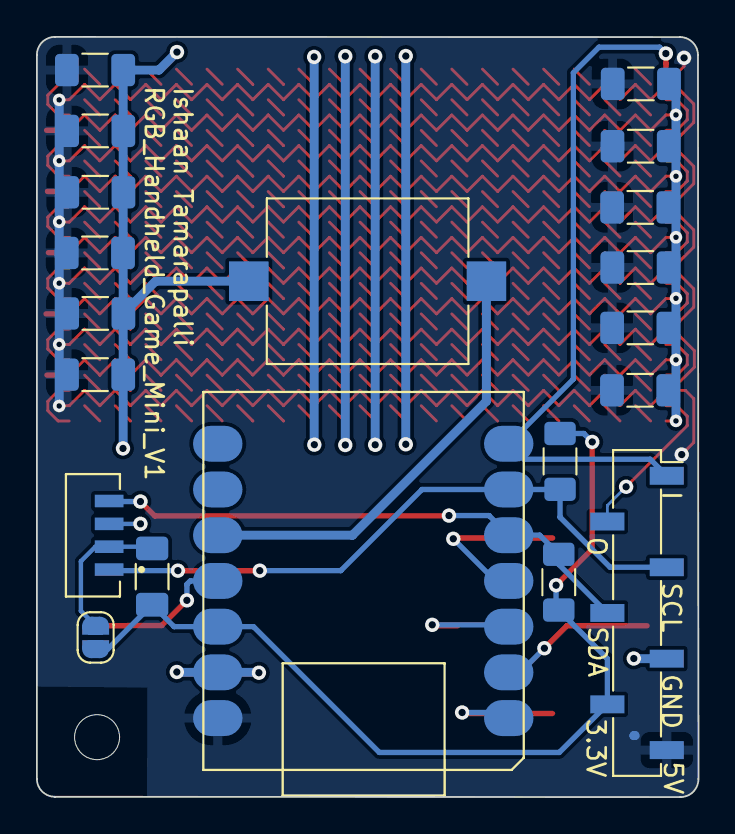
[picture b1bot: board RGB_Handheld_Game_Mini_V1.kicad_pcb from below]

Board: 2 copper layers, 36.8 x 42.2 mm, 266 parts (20 on the bottom side), 253 nets.

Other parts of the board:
R1, R2: 10k; R_1206_3216Metric_Pad1.30x1.75mm_HandSolder

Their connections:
+3.3V: R1.1, R2.1; also elsewhere on the board

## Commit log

2025-07-06 added images
2025-07-06 updated images to zoom in
2025-07-06 Added Software and Hardware folders
